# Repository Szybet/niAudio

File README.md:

# niAudio
Kobo nia ereader with audio added, using inkbox os

### Description of project structure
- apps-on-kobo - guides to compile things on kobo, for inkbox os and other things
- case - guide for the 3D printed case for the kobo nia, 3D files and pictures
- images - mostly images of the inside of kobo nia
- old - old things like stock kernel for the nia with changes for actually compiling it, some logs etc
- pcb-board - PCB + schematic for connecting the PCM2704 sound card
- discord-exports - exports of chat from discord, where progress was made. Thanks to all people that helped
- links.md - resources link that were used for research for this project
- noted.md - notes, discoveries what were important for this project
- inkbox.md - uncomplete guide for installing / creating inkbox os for the nia

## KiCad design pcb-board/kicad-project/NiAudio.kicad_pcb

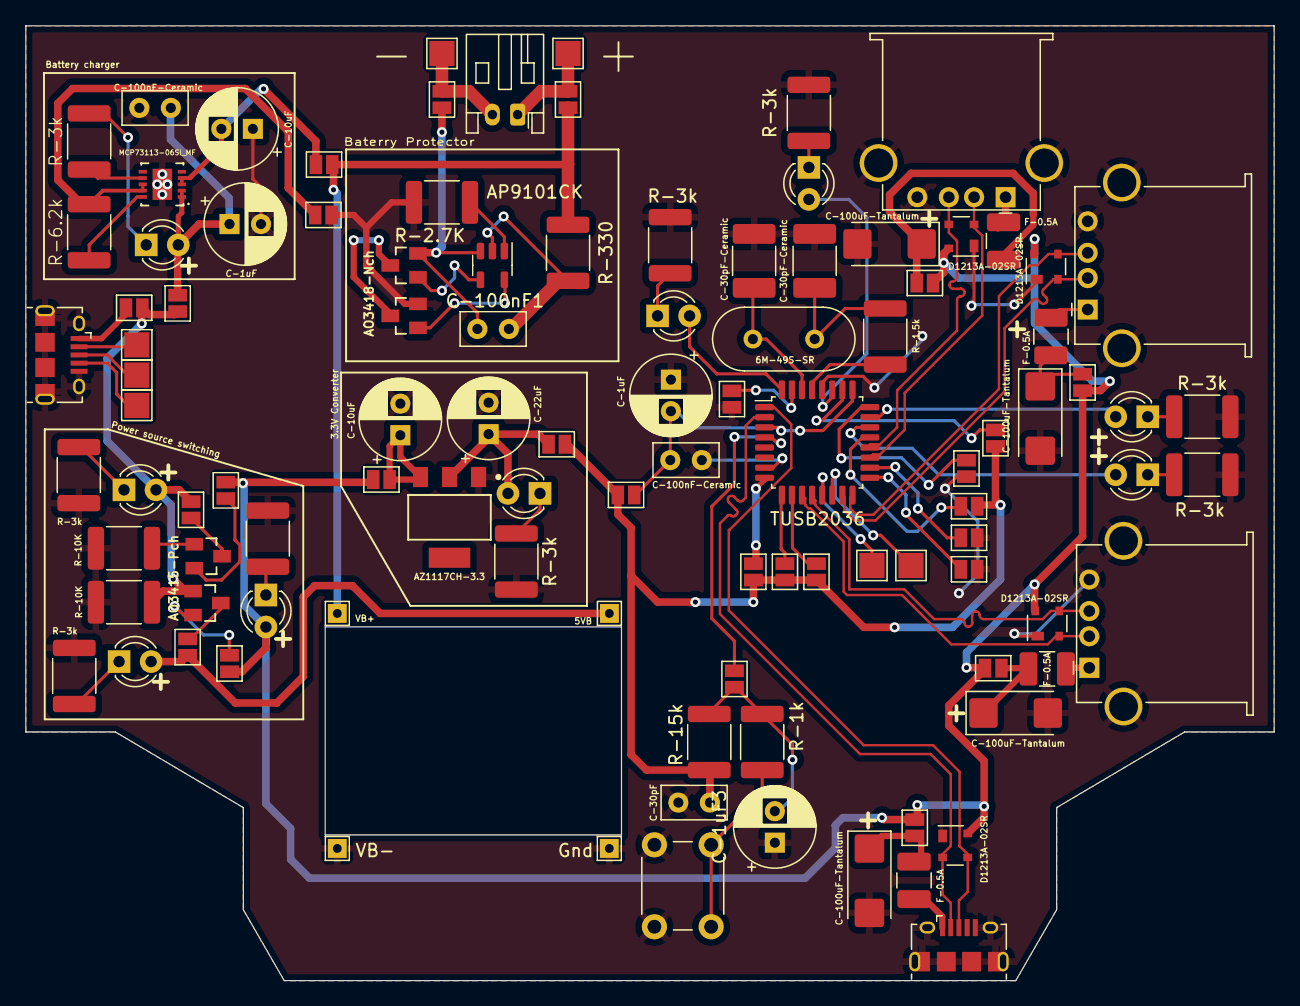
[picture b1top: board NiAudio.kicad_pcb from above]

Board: 2 copper layers, 99.0 x 75.7 mm, 104 parts (0 on the bottom side), 77 nets.

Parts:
6M-49S-SR: Crystal; Crystal_HC18-U_Vertical
AZ1117CH-3.3: AZ1117CH-3.3TRG1; DIODES_AZ1117CH-3.3TRG1_0
BT1: Battery; JST_PH_S2B-PH-K_1x02_P2.00mm_Horizontal
C-1uF, C-1uF3, C-1uF#2, C-10uF, C-22uF: C; CP_Radial_D6.3mm_P2.50mm
C-10uF#2: C_Polarized; CP_Radial_D6.3mm_P2.50mm
C-30pF, C-100nF1, C-100nF-Ceramic, C-100nF-Ceramic#2: C; C_Disc_D5.0mm_W2.5mm_P2.50mm
C-30pF-Ceramic, C-30pF-Ceramic#2: C; C_1812_4532Metric_Pad1.57x3.40mm_HandSolder
C-100uF-Tantalum, C-100uF-Tantalum#2, C-100uF-Tantalum#3, C-100uF-Tantalum#4: C; CP_EIA-6032-28_Kemet-C_Pad2.25x2.35mm_HandSolder
D1, D2, D7, D8: D1213A-02SR; SOT-143
D3, D4, D5, D6, D9, D10, D11, D12, D13: LED; LED_D3.0mm_Clear
F-0.5A, F-0.5A#2, F-0.5A#3, F-0.5A#4: Fuse; Fuse_1210_3225Metric_Pad1.42x2.65mm_HandSolder
J1: pad-VB+; TestPoint_THTPad_1.5x1.5mm_Drill0.7mm
J2: VB-; TestPoint_THTPad_1.5x1.5mm_Drill0.7mm
J3: 5VB; TestPoint_THTPad_1.5x1.5mm_Drill0.7mm
J4: Gnd; TestPoint_THTPad_1.5x1.5mm_Drill0.7mm
J5, J7, J8: USB-host; USB_A_Stewart_SS-52100-001_Horizontal
J6: USB_B_Host; USB_Micro-B_Amphenol_10118194_Horizontal
J9: USB_B_Micro_charger; USB_Micro-B_Amphenol_10118194_Horizontal
J10, J11, J12, J15, J16: pad; TestPoint_Pad_2.0x2.0mm
J13, J14: pad-VB-; TestPoint_Pad_2.0x2.0mm
JP1, JP2, JP3, JP4, JP5, JP6, JP7, JP8, JP9, JP10, JP11, JP12, JP13, JP14, JP15, JP16, JP17, JP18, JP19, JP20, JP21, JP22, JP23, JP25, JP26, JP28, JP29: SolderJumper_2_Open; SolderJumper-2_P1.3mm_Open_Pad1.0x1.5mm
Q1, Q2: AO3418-Nch; SOT-23
Q3, Q4: AO3415-Pch; SOT-23
R1, R2, R3: R-3k; R_1812_4532Metric_Pad1.30x3.40mm_HandSolder
R-1.5k, R-1k, R-2.7K, R-3k, R-3k1, R-3k#2, R-3k#3, R-3k#4, R-3k#5, R-6.2k, R-10K, R-10K#2, R-15k, R-330: R; R_1812_4532Metric_Pad1.30x3.40mm_HandSolder
SW1: RESET-Btn; SW_PUSH_6mm
U1: AP9101CK; SOT-23-5
U2: MCP73113-06SI_MF; Microchip-MCP73113-06SI_MF-Manufacturer_Recommended
U3: TUSB2036; LQFP-32_7x7mm_P0.8mm

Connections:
/3.3V: C-30pF.2, JP16.2 (B), JP17.1 (A), JP18.1 (A), JP20.1 (A), JP22.2 (B), JP23.2 (B), JP26.2 (B), R-15k.2
/5VB: D4.2 (A), J3.1, JP8.2 (B)
/5VC: D3.2 (A), JP7.1 (A), JP11.2 (B), JP14.2 (B), Q4.1, R-10K#2.1
/5VM: D1.4 (VCC/Vn), D2.4 (VCC/Vn), D5.2 (A), D7.4 (VCC/Vn), D8.4 (VCC/Vn), JP4.2 (B), JP5.2 (B), JP9.2 (B), JP10.2 (B), JP12.1 (A), JP13.2 (B), JP15.2 (B)
/G1+: D1.3 (CH2), J5.3 (D+), U3.12 (DP1)
/G1-: D1.2 (CH1), J5.2 (D-), U3.11 (DM1)
/G2+: D7.3 (CH2), J7.3 (D+), U3.16 (DP2)
/G2-: D7.2 (CH1), J7.2 (D-), U3.15 (DM2)
/G3+: D8.3 (CH2), J8.3 (D+), U3.20 (DP3)
/G3-: D8.2 (CH1), J8.2 (D-), U3.19 (DM3)
/H+: D2.3 (CH2), J6.3 (D+), U3.1 (DP0)
/H-: D2.2 (CH1), J6.2 (D-), U3.2 (DM0)
/RST: JP29.2 (B), U3.4 (~RESET)
/VB+: J1.1, JP1.2 (B), JP3.1 (A), R-330.1
GND: AZ1117CH-3.3.1 (GND), C-1uF.1, C-1uF3.1, C-1uF#2.1, C-10uF.2, C-10uF#2.2, C-22uF.2, C-30pF.1, C-30pF-Ceramic.2, C-30pF-Ceramic#2.1, C-100nF-Ceramic.2, C-100nF-Ceramic#2.2, C-100uF-Tantalum.2, C-100uF-Tantalum#2.2, C-100uF-Tantalum#3.2, C-100uF-Tantalum#4.2, D1.1 (GND/Vn), D2.1 (GND/Vn), D7.1 (GND/Vn), D8.1 (GND/Vn), J2.1, J4.1, J5.4 (GND), J5.5 (Shield), J6.5 (GND), J6.6 (Shield), J7.4 (GND), J7.5 (Shield), J8.4 (GND), J8.5 (Shield), J9.5 (GND), J9.6 (Shield), JP6.1 (A), JP19.1 (A), JP21.1 (A), JP25.2 (B), JP28.2 (B), Q2.2, R2.2, R3.2, R-2.7K.2, R-3k.2, R-3k1.2, R-3k#2.2, R-3k#3.2, R-3k#4.2, R-3k#5.2, R-10K.2, R-10K#2.2, SW1.2, U2.11 (EP), U3.7 (GND), U3.28 (GND)
unnamed: 6M-49S-SR.1, C-30pF-Ceramic#2.2, R-1.5k.2
unnamed: 6M-49S-SR.2, C-30pF-Ceramic.1, U3.30 (XTAL1/CLK48)
unnamed: AZ1117CH-3.3.2 (OUTPUT), C-22uF.1, D13.2 (A), JP16.1 (A)
unnamed: AZ1117CH-3.3.3 (INPUT), C-10uF.1, JP12.2 (B)
unnamed: BT1.1 (+), J15.1, JP1.1 (A)
unnamed: BT1.2 (-), J16.1, JP2.1 (A)
unnamed: C-1uF.2, JP3.2 (B), U2.3 (VBAT), U2.4 (VBAT)
unnamed: C-1uF3.2, JP29.1 (A), R-1k.2, R-15k.1
unnamed: C-100nF1.1, JP2.2 (B), Q1.2, U1.3 (VSS)
unnamed: C-100nF1.2, R-330.2, U1.2 (VDD)
unnamed: C-10uF#2.1, C-100nF-Ceramic.1, D6.2 (A), JP11.1 (A), U2.1 (VDD), U2.2 (VDD)
unnamed: C-1uF#2.2, C-100nF-Ceramic#2.1, JP22.1 (A), U3.3 (VCC), U3.25 (VCC)
unnamed: C-100uF-Tantalum.1, F-0.5A#3.2, JP5.1 (A)
unnamed: C-100uF-Tantalum#4.1, F-0.5A#4.2, JP4.1 (A)
unnamed: C-100uF-Tantalum#2.1, F-0.5A#2.2, JP13.1 (A)
unnamed: C-100uF-Tantalum#3.1, F-0.5A.2, JP15.1 (A)
unnamed: D3.1 (K), R2.1
unnamed: D4.1 (K), R3.1
unnamed: D5.1 (K), R-3k1.1
unnamed: D6.1 (K), R1.1
unnamed: D9.1 (K), R-3k.1
unnamed: D9.2 (A), U3.22 (NPINT0)
unnamed: D10.1 (K), R-3k#4.1
unnamed: D10.2 (A), U3.23 (NPINT1)
unnamed: D11.1 (K), R-3k#3.1
unnamed: D11.2 (A), U3.27 (DP0PUR)
unnamed: D12.1 (K), R-3k#5.1
unnamed: D12.2 (A), U3.32 (SUSPND)
unnamed: D13.1 (K), R-3k#2.1
unnamed: F-0.5A#3.1, J5.1 (VBUS)
unnamed: F-0.5A#4.1, J6.1 (VBUS)
unnamed: F-0.5A#2.1, J7.1 (VBUS)
unnamed: F-0.5A.1, J8.1 (VBUS)
unnamed: J9.1 (VBUS), JP14.1 (A)
unnamed: J9.3 (D+), J10.1
unnamed: J9.2 (D-), J11.1
unnamed: J9.4 (ID), J12.1
unnamed: J13.1, U3.13 (~PWRON2)
unnamed: J14.1, U3.14 (~OVRCUR2)
unnamed: JP6.2 (B), R-6.2k.2, U2.8 (VSS), U2.9 (VSS)
unnamed: JP7.2 (B), Q3.3
unnamed: JP8.1 (A), Q4.3
unnamed: JP9.1 (A), Q3.2
unnamed: JP10.1 (A), Q4.2
unnamed: JP17.2 (B), U3.8 (~BUSPWR)
unnamed: JP18.2 (B), U3.21 (~OCPROT/~PWRSW)
unnamed: JP19.2 (B), U3.24 (~NP3)
unnamed: JP20.2 (B), U3.26 (~EXTMEM)
unnamed: JP21.2 (B), U3.31 (MODE)
unnamed: JP23.1 (A), U3.9 (~PWRON1)
unnamed: JP25.1 (A), U3.17 (~PWRON3)
unnamed: JP26.1 (A), U3.10 (~OVRCUR1)
unnamed: JP28.1 (A), U3.18 (~OVRCUR3)
unnamed: Q1.1, U1.4 (DO)
unnamed: Q1.3, Q2.3
unnamed: Q2.1, U1.5 (CO)
unnamed: Q3.1, R-10K.1
unnamed: R1.2, U2.7 (STAT)
unnamed: R-1.5k.1, U3.29 (XTAL2)
unnamed: R-1k.1, SW1.1
unnamed: R-2.7K.1, U1.1 (VM)
unnamed: R-6.2k.1, U2.10 (PROG)

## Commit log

2022-02-15 first
2022-02-16 Create ntx_hwconfig
2022-02-16 Create ntx_hwconfig-more
2022-02-17 update working now?
2022-02-17 usbmonitor
2022-02-17 Create uart-custom-kernel
2022-02-18 work
2022-02-18 oryginal from update
2022-02-18 i can't trust copying from now on
2022-02-19 bootloaderrr
2022-02-19 images
2022-02-26 Misc fixes
2022-03-05 Notes for tux-linux
2022-03-05 markdown fixes
2022-04-17 qt guide
2022-04-19 dev on kobo
2022-04-22 Create gitignore
2022-04-22 cleaning
2022-04-23 Update gitignore-example
2022-05-06 folder
2022-08-02 pcb init
2022-08-05 ready schematic
2022-08-05 footprints annotations
2022-08-06 almost ready pcb
2022-08-07 pcb finish
2022-08-08 minor things
2022-08-08 case
2022-08-08 3d files
2022-08-08 cleaning...
2022-08-08 cleaning cleaning
2022-08-27 images, fcc
2022-09-27 discord exports
2022-11-21 pdf backup
2023-03-11 keyboard init
2023-03-11 Create LICENSE
2023-05-15 Create libxslt
2023-05-15 Rename libxslt to libxslt.md
2023-05-15 Create polkit
2023-05-15 Rename polkit to polkit.md
2023-05-21 cleaning a bit
2023-05-21 scripts things
2023-05-21 binaries
2023-06-26 audio nia kernel config
2023-07-25 nheko and config update
